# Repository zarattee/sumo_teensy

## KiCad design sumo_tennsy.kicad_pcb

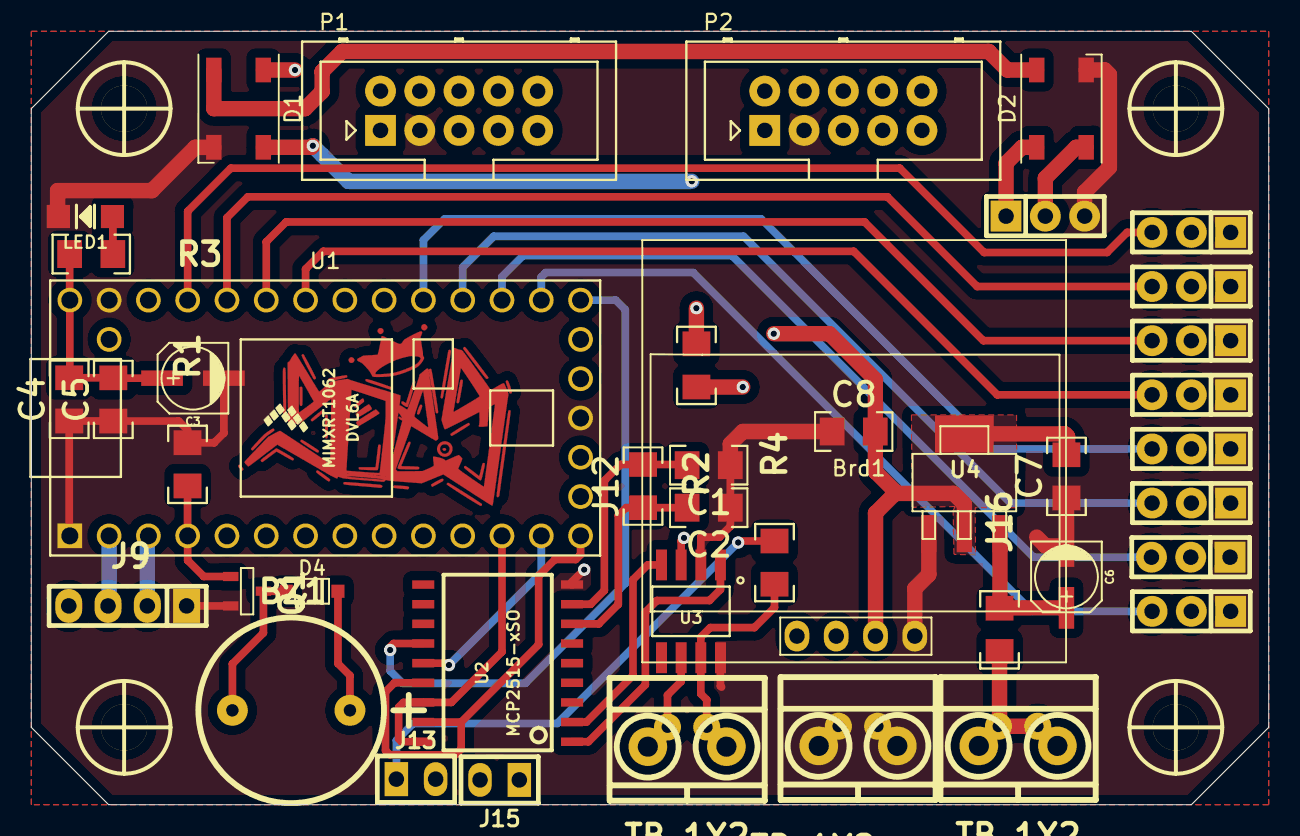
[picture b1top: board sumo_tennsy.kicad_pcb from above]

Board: 4 copper layers, 80.0 x 50.0 mm, 46 parts (0 on the bottom side), 39 nets.

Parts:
BZ1: Buzzer; Buzzer_12mm
Brd1: SSD1306; 128x64OLED
C1, C2, C4, C5, C7, C8: C; C_1206
C3: CAPAPOL; CAP_ELEC_SMD_4X5.5
C6: 100uf; CAP_ELEC_SMD_4X5.5
D1, D2: WS2812B; LED_WS2812B-PLCC4
D4: DIODE; sod123
J1, J2, J3, J4, J5, J6, J7, J8, J17: CONN_01X03; Pin_Strip_3
J9: HEADER_4; pin_strip_4
J10, J11, J14: TB_1X2; BORNERA2_DUO
J12: HEADER_2; C_1206
J13, J15: HEADER_2; Pin_strip_2
J16: HEADER_2; R_1206
LED1: LED; LED_1206
P1, P2: HEADER_02X05; Header_2x05x2.54mm_Vertical
Q1: 2N7002; SOT23
R1, R2, R3, R4: R; R_1206
U1: Teensy4.0; Teensy40
U2: MCP2515-xSO; SOIC-18
U3: TJA1050; SOIC-8_Hand_Soldering
U4: LM1117-SOT; SOT223
hole_3mm, hole_3mm#2, hole_3mm#3, hole_3mm#4: VAL**; hole_3mm

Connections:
+5V: Brd1.2, C3.1, C4.1, C5.1, C7.1, C8.1, D1.1, D2.1, J1.2, J2.2, J3.2, J4.2, J5.2, J6.2, J7.2, J8.2, J9.4, J17.1, P1.4, P1.7, P1.8, P2.4, P2.7, P2.8, R3.1, U1.33, U3.3, U4.2, U4.4
/A0: J8.3, U1.21
/A1: J7.3, U1.22
/A2: J6.3, U1.23
/A3: J5.3, U1.24
/A6: J4.3, U1.27
/A7: J3.3, U1.28
/A8: J2.3, U1.29
/A9: J1.3, U1.30
/BUZZER: Q1.1, R1.1, U1.4
/CS: U1.12, U2.16
/LED: R2.2, U1.7
/M1A: P1.9, U1.11
/M1B: P1.10, U1.10
/M2A: P2.9, U1.9
/M2B: P2.10, U1.8
/RX1: J9.3, U1.2
/SCK: U1.20, U2.13
/SCL: Brd1.3, U1.26
/SDA: Brd1.4, U1.25
/SI: U1.13, U2.14
/SO: U1.14, U2.15
/TX1: J9.2, U1.3
/VIN: J10.1, J10.2, J16.1
GND: Brd1.1, C1.2, C2.2, C3.2, C4.2, C5.2, C6.2, C7.2, C8.2, D1.3, D2.3, J1.1, J2.1, J3.1, J4.1, J5.1, J6.1, J7.1, J8.1, J9.1, J11.1, J11.2, J17.3, LED1.2, P1.3, P2.3, Q1.3, R1.2, U1.1, U1.17, U1.32, U2.9, U3.2, U3.8, U4.1
unnamed: BZ1.1, D4.2
unnamed: BZ1.2, D4.1, Q1.2
unnamed: C1.1, J12.1, U2.8
unnamed: C2.1, J12.2, U2.7
unnamed: C6.1, J16.2, U4.3
unnamed: D1.2, D2.4
unnamed: D1.4, R2.1
unnamed: D2.2, J17.2
unnamed: J13.1, R4.2
unnamed: J13.2, J14.1, J15.2, U3.6
unnamed: J14.2, J15.1, R4.1, U3.7
unnamed: LED1.1, R3.2
unnamed: U2.1, U3.1
unnamed: U2.2, U3.4

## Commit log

2020-12-13 commit inicial
2020-12-23 modifcaciones
    se agrego vista 3d y se modifico pcb
